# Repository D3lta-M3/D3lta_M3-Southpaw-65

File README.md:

# D3lta_M3 Southpaw 65
 65% keyboard, with either a macropad or a numpad on the left hand side. Uses through-hole for soldering

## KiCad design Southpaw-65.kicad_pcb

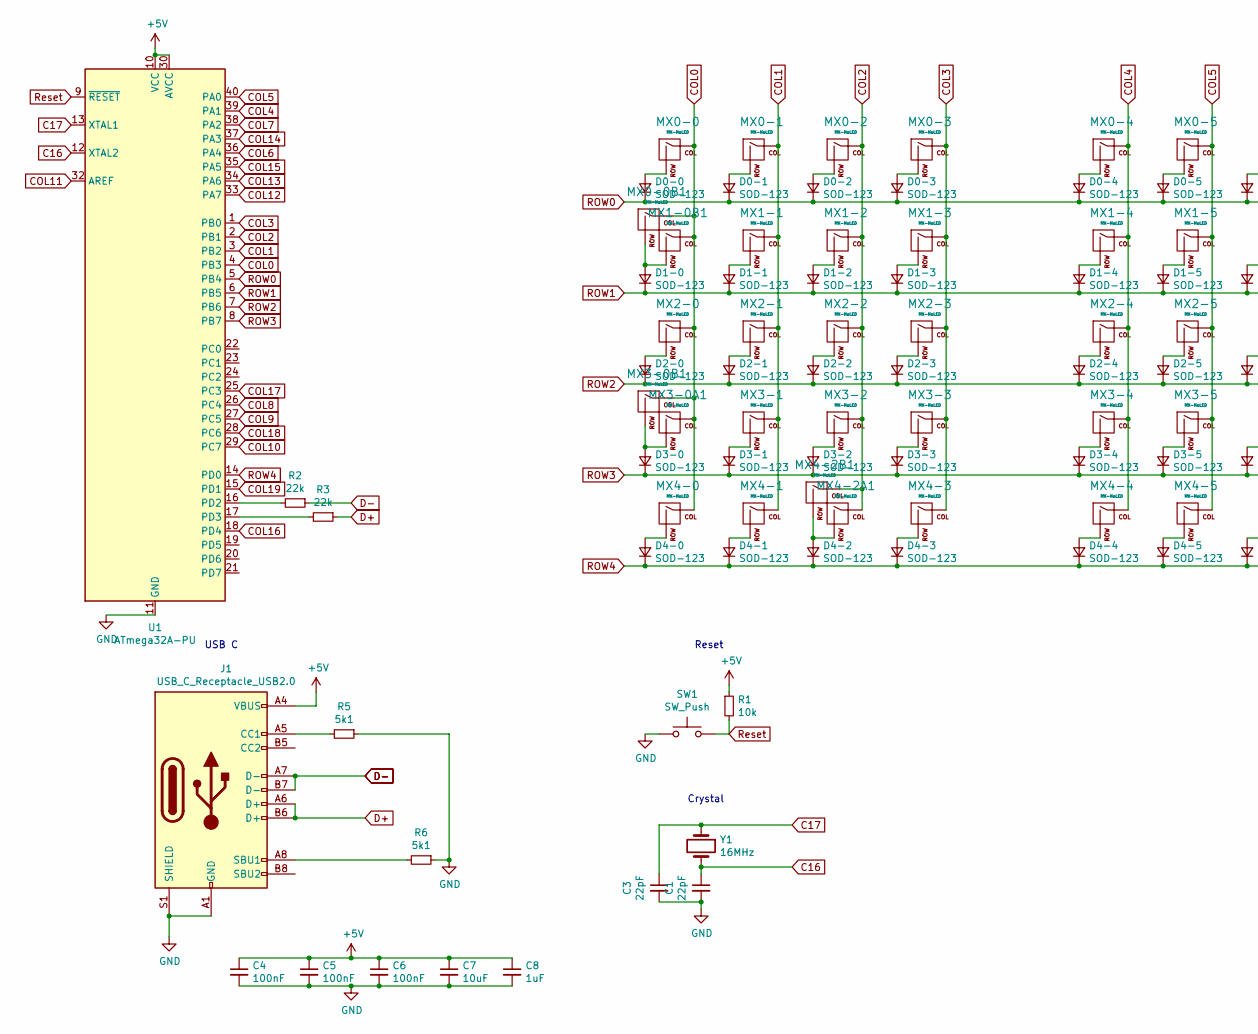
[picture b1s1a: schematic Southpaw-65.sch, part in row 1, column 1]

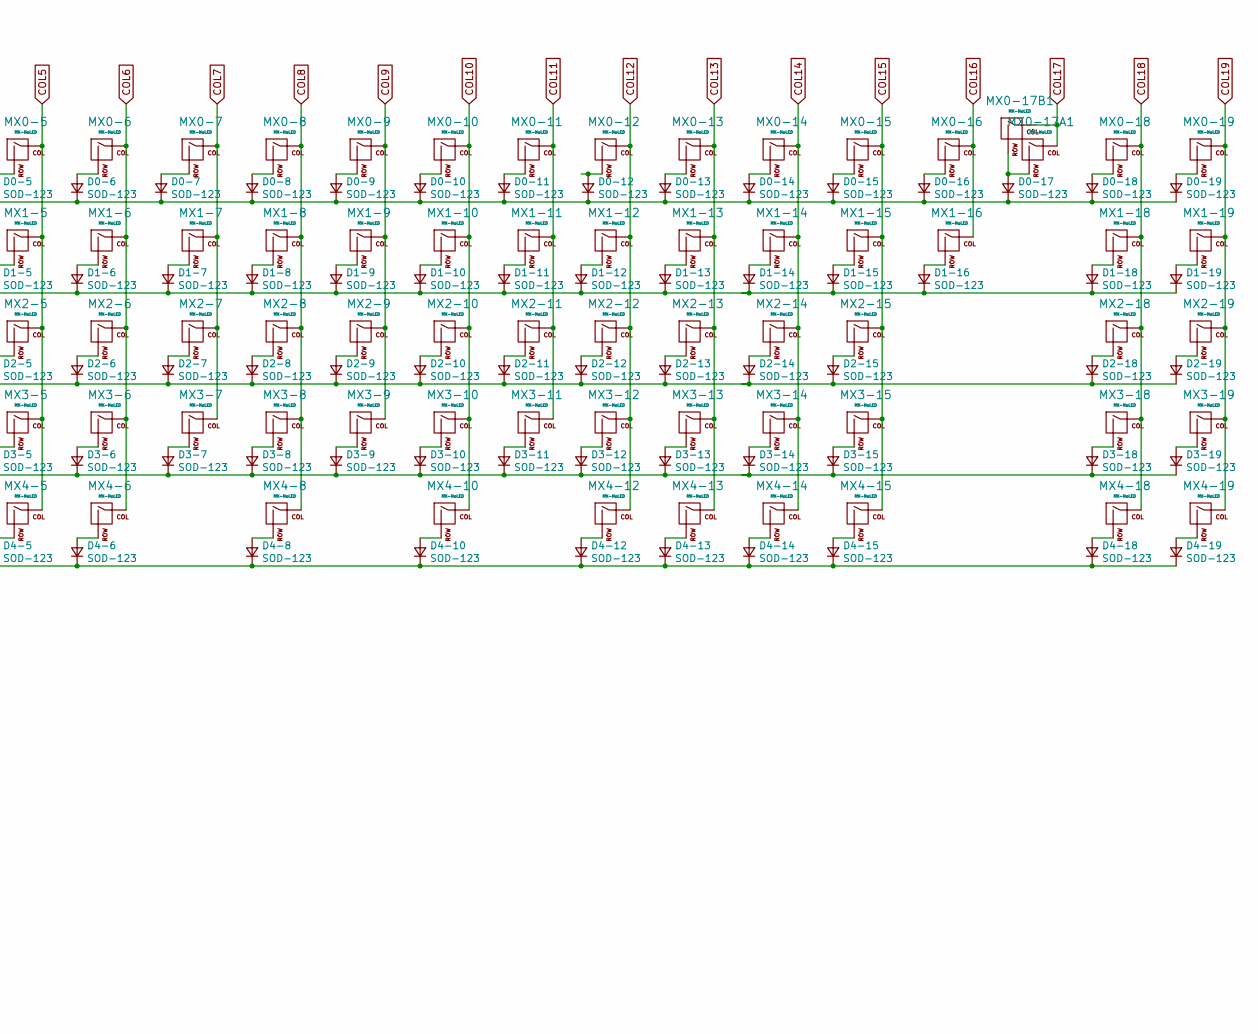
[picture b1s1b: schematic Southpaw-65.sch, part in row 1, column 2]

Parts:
C1, C3: 22pF; CP_Radial_Tantal_D5.0mm_P2.50mm
C4, C5, C6: 100nF; CP_Radial_Tantal_D5.0mm_P2.50mm
C7: 10uF; CP_Radial_Tantal_D5.0mm_P2.50mm
C8: 1uF; CP_Radial_D18.0mm_P7.50mm
D0-0, D0-1, D0-2, D0-3, D0-4, D0-5, D0-6, D0-7, D0-8, D0-9, D0-10, D0-11, D0-12, D0-13, D0-14, D0-15, D0-16, D0-17, D0-18, D0-19, D1-0, D1-1, D1-2, D1-3, D1-4, D1-5, D1-6, D1-7, D1-8, D1-9, D1-10, D1-11, D1-12, D1-13, D1-14, D1-15, D1-16, D1-18, D1-19, D2-0, D2-1, D2-2, D2-3, D2-4, D2-5, D2-6, D2-7, D2-8, D2-9, D2-10, D2-11, D2-12, D2-13, D2-14, D2-15, D2-18, D2-19, D3-0, D3-1, D3-2, D3-3, D3-4, D3-5, D3-6, D3-7, D3-8, D3-9, D3-10, D3-11, D3-12, D3-13, D3-14, D3-15, D3-18, D3-19, D4-0, D4-1, D4-2, D4-3, D4-4, D4-5, D4-6, D4-8, D4-10, D4-12, D4-13, D4-14, D4-15, D4-18, D4-19: SOD-123; D_DO-41_SOD81_P7.62mm_Horizontal
J1: USB_C_Receptacle_USB2.0; USB_C_Receptacle_GCT_USB4085
MX0-0, MX0-1, MX0-2, MX0-3, MX0-4, MX0-5, MX0-6, MX0-7, MX0-8, MX0-9, MX0-10, MX0-11, MX0-12, MX0-13, MX0-14, MX0-15, MX0-16, MX0-17A1, MX0-18, MX0-19, MX1-0B1, MX1-1, MX1-2, MX1-3, MX1-5, MX1-6, MX1-7, MX1-8, MX1-9, MX1-10, MX1-11, MX1-12, MX1-13, MX1-14, MX1-15, MX1-16, MX1-19, MX2-0, MX2-1, MX2-2, MX2-3, MX2-5, MX2-6, MX2-7, MX2-8, MX2-9, MX2-10, MX2-11, MX2-12, MX2-13, MX2-14, MX2-15, MX2-19, MX3-0A1, MX3-1, MX3-2, MX3-3, MX3-5, MX3-6, MX3-7, MX3-8, MX3-9, MX3-10, MX3-11, MX3-12, MX3-13, MX3-14, MX3-18, MX3-19, MX4-0, MX4-1, MX4-2A1, MX4-3, MX4-14, MX4-15, MX4-18, MX4-19: MX-NoLED; MXOnly-1U
MX0-0B1, MX0-17B1, MX3-0B1, MX4-2B1: MX-NoLED; MXOnly-2U
MX1-4, MX1-18: MX-NoLED; MXOnly-1.5U
MX2-4, MX3-15: MX-NoLED; MXOnly-1.75U
MX2-18, MX3-4: MX-NoLED; MXOnly-2.25U
MX4-4, MX4-5, MX4-6, MX4-13: MX-NoLED; MXOnly-1.25U
MX4-8, MX4-12: MX-NoLED; MXOnly-3U
MX4-10: MX-NoLED; MXOnly-7U
R1: 10k; R_Axial_DIN0207_L6.3mm_D2.5mm_P7.62mm_Horizontal
R2, R3: 22k; R_Axial_DIN0207_L6.3mm_D2.5mm_P7.62mm_Horizontal
R5, R6: 5k1; R_Axial_DIN0207_L6.3mm_D2.5mm_P7.62mm_Horizontal
SW1: SW_Push; PushButton_6x6mm_TH
U1: ATmega32A-PU; DIP-40_W15.24mm
Y1: 16MHz; Crystal_HC49-U_Horizontal

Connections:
+5V: C4.1, C5.1, C6.1, C7.1, C8.1, J1.A4 (VBUS), J1.A9 (VBUS), J1.B4 (VBUS), J1.B9 (VBUS), R1.1, U1.10 (VCC), U1.30 (AVCC)
C16: C1.1, U1.12 (XTAL2), Y1.2
C17: C3.1, U1.13 (XTAL1), Y1.1
COL0: MX0-0.1 (COL), MX0-0B1.1 (COL), MX1-0B1.1 (COL), MX2-0.1 (COL), MX3-0A1.1 (COL), MX3-0B1.1 (COL), MX4-0.1 (COL), U1.4 (PB3)
COL1: MX0-1.1 (COL), MX1-1.1 (COL), MX2-1.1 (COL), MX3-1.1 (COL), MX4-1.1 (COL), U1.3 (PB2)
COL2: MX0-2.1 (COL), MX1-2.1 (COL), MX2-2.1 (COL), MX3-2.1 (COL), MX4-2A1.1 (COL), MX4-2B1.1 (COL), U1.2 (PB1)
COL3: MX0-3.1 (COL), MX1-3.1 (COL), MX2-3.1 (COL), MX3-3.1 (COL), MX4-3.1 (COL), U1.1 (PB0)
COL4: MX0-4.1 (COL), MX1-4.1 (COL), MX2-4.1 (COL), MX3-4.1 (COL), MX4-4.1 (COL), U1.39 (PA1)
COL5: MX0-5.1 (COL), MX1-5.1 (COL), MX2-5.1 (COL), MX3-5.1 (COL), MX4-5.1 (COL), U1.40 (PA0)
COL6: MX0-6.1 (COL), MX1-6.1 (COL), MX2-6.1 (COL), MX3-6.1 (COL), MX4-6.1 (COL), U1.36 (PA4)
COL7: MX0-7.1 (COL), MX1-7.1 (COL), MX2-7.1 (COL), MX3-7.1 (COL), U1.38 (PA2)
COL8: MX0-8.1 (COL), MX1-8.1 (COL), MX2-8.1 (COL), MX3-8.1 (COL), MX4-8.1 (COL), U1.26 (PC4)
COL9: MX0-9.1 (COL), MX1-9.1 (COL), MX2-9.1 (COL), MX3-9.1 (COL), U1.27 (PC5)
COL10: MX0-10.1 (COL), MX1-10.1 (COL), MX2-10.1 (COL), MX3-10.1 (COL), MX4-10.1 (COL), U1.29 (PC7)
COL11: MX0-11.1 (COL), MX1-11.1 (COL), MX2-11.1 (COL), MX3-11.1 (COL), U1.32 (AREF)
COL12: MX0-12.1 (COL), MX1-12.1 (COL), MX2-12.1 (COL), MX3-12.1 (COL), MX4-12.1 (COL), U1.33 (PA7)
COL13: MX0-13.1 (COL), MX1-13.1 (COL), MX2-13.1 (COL), MX3-13.1 (COL), MX4-13.1 (COL), U1.34 (PA6)
COL14: MX0-14.1 (COL), MX1-14.1 (COL), MX2-14.1 (COL), MX3-14.1 (COL), MX4-14.1 (COL), U1.37 (PA3)
COL15: MX0-15.1 (COL), MX1-15.1 (COL), MX2-15.1 (COL), MX3-15.1 (COL), MX4-15.1 (COL), U1.35 (PA5)
COL16: MX0-16.1 (COL), MX1-16.1 (COL), U1.18 (PD4)
COL17: MX0-17A1.1 (COL), MX0-17B1.1 (COL), U1.25 (PC3)
COL18: MX0-18.1 (COL), MX1-18.1 (COL), MX2-18.1 (COL), MX3-18.1 (COL), MX4-18.1 (COL), U1.28 (PC6)
COL19: MX0-19.1 (COL), MX1-19.1 (COL), MX2-19.1 (COL), MX3-19.1 (COL), MX4-19.1 (COL), U1.15 (PD1)
D+: J1.A6 (D+), J1.B6 (D+), R3.1
D-: J1.A7 (D-), J1.B7 (D-), R2.1
GND: C1.2, C3.2, C4.2, C5.2, C6.2, C7.2, C8.2, J1.A1 (GND), J1.A12 (GND), J1.B1 (GND), J1.B12 (GND), J1.S1 (SHIELD), R5.1, R6.1, SW1.1, U1.11 (GND), U1.31 (GND)
unnamed: D0-0.2 (A), MX0-0.2 (ROW)
unnamed: D0-1.2 (A), MX0-1.2 (ROW)
unnamed: D0-2.2 (A), MX0-2.2 (ROW)
unnamed: D0-3.2 (A), MX0-3.2 (ROW)
unnamed: D0-4.2 (A), MX0-4.2 (ROW)
unnamed: D0-5.2 (A), MX0-5.2 (ROW)
unnamed: D0-6.2 (A), MX0-6.2 (ROW)
unnamed: D0-7.2 (A), MX0-7.2 (ROW)
unnamed: D0-8.2 (A), MX0-8.2 (ROW)
unnamed: D0-9.2 (A), MX0-9.2 (ROW)
unnamed: D0-10.2 (A), MX0-10.2 (ROW)
unnamed: D0-11.2 (A), MX0-11.2 (ROW)
unnamed: D0-12.2 (A), MX0-12.2 (ROW)
unnamed: D0-13.2 (A), MX0-13.2 (ROW)
unnamed: D0-14.2 (A), MX0-14.2 (ROW)
unnamed: D0-15.2 (A), MX0-15.2 (ROW)
unnamed: D0-16.2 (A), MX0-16.2 (ROW)
unnamed: D0-17.2 (A), MX0-17A1.2 (ROW), MX0-17B1.2 (ROW)
unnamed: D0-18.2 (A), MX0-18.2 (ROW)
unnamed: D0-19.2 (A), MX0-19.2 (ROW)
unnamed: D1-0.2 (A), MX0-0B1.2 (ROW), MX1-0B1.2 (ROW)
unnamed: D1-1.2 (A), MX1-1.2 (ROW)
unnamed: D1-2.2 (A), MX1-2.2 (ROW)
unnamed: D1-3.2 (A), MX1-3.2 (ROW)
unnamed: D1-4.2 (A), MX1-4.2 (ROW)
unnamed: D1-5.2 (A), MX1-5.2 (ROW)
unnamed: D1-6.2 (A), MX1-6.2 (ROW)
unnamed: D1-7.2 (A), MX1-7.2 (ROW)
unnamed: D1-8.2 (A), MX1-8.2 (ROW)
unnamed: D1-9.2 (A), MX1-9.2 (ROW)
unnamed: D1-10.2 (A), MX1-10.2 (ROW)
unnamed: D1-11.2 (A), MX1-11.2 (ROW)
unnamed: D1-12.2 (A), MX1-12.2 (ROW)
unnamed: D1-13.2 (A), MX1-13.2 (ROW)
unnamed: D1-14.2 (A), MX1-14.2 (ROW)
unnamed: D1-15.2 (A), MX1-15.2 (ROW)
unnamed: D1-16.2 (A), MX1-16.2 (ROW)
unnamed: D1-18.2 (A), MX1-18.2 (ROW)
unnamed: D1-19.2 (A), MX1-19.2 (ROW)
unnamed: D2-0.2 (A), MX2-0.2 (ROW)
unnamed: D2-1.2 (A), MX2-1.2 (ROW)
unnamed: D2-2.2 (A), MX2-2.2 (ROW)
unnamed: D2-3.2 (A), MX2-3.2 (ROW)
unnamed: D2-4.2 (A), MX2-4.2 (ROW)
unnamed: D2-5.2 (A), MX2-5.2 (ROW)
unnamed: D2-6.2 (A), MX2-6.2 (ROW)
unnamed: D2-7.2 (A), MX2-7.2 (ROW)
unnamed: D2-8.2 (A), MX2-8.2 (ROW)
unnamed: D2-9.2 (A), MX2-9.2 (ROW)
unnamed: D2-10.2 (A), MX2-10.2 (ROW)
unnamed: D2-11.2 (A), MX2-11.2 (ROW)
unnamed: D2-12.2 (A), MX2-12.2 (ROW)
unnamed: D2-13.2 (A), MX2-13.2 (ROW)
unnamed: D2-14.2 (A), MX2-14.2 (ROW)
unnamed: D2-15.2 (A), MX2-15.2 (ROW)
unnamed: D2-18.2 (A), MX2-18.2 (ROW)
unnamed: D2-19.2 (A), MX2-19.2 (ROW)
unnamed: D3-0.2 (A), MX3-0A1.2 (ROW), MX3-0B1.2 (ROW)
unnamed: D3-1.2 (A), MX3-1.2 (ROW)
unnamed: D3-2.2 (A), MX3-2.2 (ROW)
unnamed: D3-3.2 (A), MX3-3.2 (ROW)
unnamed: D3-4.2 (A), MX3-4.2 (ROW)
unnamed: D3-5.2 (A), MX3-5.2 (ROW)
unnamed: D3-6.2 (A), MX3-6.2 (ROW)
unnamed: D3-7.2 (A), MX3-7.2 (ROW)
unnamed: D3-8.2 (A), MX3-8.2 (ROW)
unnamed: D3-9.2 (A), MX3-9.2 (ROW)
unnamed: D3-10.2 (A), MX3-10.2 (ROW)
unnamed: D3-11.2 (A), MX3-11.2 (ROW)
unnamed: D3-12.2 (A), MX3-12.2 (ROW)
unnamed: D3-13.2 (A), MX3-13.2 (ROW)
unnamed: D3-14.2 (A), MX3-14.2 (ROW)
unnamed: D3-15.2 (A), MX3-15.2 (ROW)
unnamed: D3-18.2 (A), MX3-18.2 (ROW)
unnamed: D3-19.2 (A), MX3-19.2 (ROW)
unnamed: D4-0.2 (A), MX4-0.2 (ROW)
unnamed: D4-1.2 (A), MX4-1.2 (ROW)
unnamed: D4-2.2 (A), MX4-2A1.2 (ROW), MX4-2B1.2 (ROW)
unnamed: D4-3.2 (A), MX4-3.2 (ROW)
unnamed: D4-4.2 (A), MX4-4.2 (ROW)
unnamed: D4-5.2 (A), MX4-5.2 (ROW)
unnamed: D4-6.2 (A), MX4-6.2 (ROW)
unnamed: D4-8.2 (A), MX4-8.2 (ROW)
unnamed: D4-10.2 (A), MX4-10.2 (ROW)
unnamed: D4-12.2 (A), MX4-12.2 (ROW)
unnamed: D4-13.2 (A), MX4-13.2 (ROW)
unnamed: D4-14.2 (A), MX4-14.2 (ROW)
unnamed: D4-15.2 (A), MX4-15.2 (ROW)
unnamed: D4-18.2 (A), MX4-18.2 (ROW)
unnamed: D4-19.2 (A), MX4-19.2 (ROW)
unnamed: J1.A5 (CC1), R5.2
unnamed: J1.A8 (SBU1), R6.2
unnamed: R2.2, U1.16 (PD2)
unnamed: R3.2, U1.17 (PD3)
ROW0: D0-0.1 (K), D0-1.1 (K), D0-2.1 (K), D0-3.1 (K), D0-4.1 (K), D0-5.1 (K), D0-6.1 (K), D0-7.1 (K), D0-8.1 (K), D0-9.1 (K), D0-10.1 (K), D0-11.1 (K), D0-12.1 (K), D0-13.1 (K), D0-14.1 (K), D0-15.1 (K), D0-16.1 (K), D0-17.1 (K), D0-18.1 (K), D0-19.1 (K), U1.5 (PB4)
ROW1: D1-0.1 (K), D1-1.1 (K), D1-2.1 (K), D1-3.1 (K), D1-4.1 (K), D1-5.1 (K), D1-6.1 (K), D1-7.1 (K), D1-8.1 (K), D1-9.1 (K), D1-10.1 (K), D1-11.1 (K), D1-12.1 (K), D1-13.1 (K), D1-14.1 (K), D1-15.1 (K), D1-16.1 (K), D1-18.1 (K), D1-19.1 (K), U1.6 (PB5)
ROW2: D2-0.1 (K), D2-1.1 (K), D2-2.1 (K), D2-3.1 (K), D2-4.1 (K), D2-5.1 (K), D2-6.1 (K), D2-7.1 (K), D2-8.1 (K), D2-9.1 (K), D2-10.1 (K), D2-11.1 (K), D2-12.1 (K), D2-13.1 (K), D2-14.1 (K), D2-15.1 (K), D2-18.1 (K), D2-19.1 (K), U1.7 (PB6)
ROW3: D3-0.1 (K), D3-1.1 (K), D3-2.1 (K), D3-3.1 (K), D3-4.1 (K), D3-5.1 (K), D3-6.1 (K), D3-7.1 (K), D3-8.1 (K), D3-9.1 (K), D3-10.1 (K), D3-11.1 (K), D3-12.1 (K), D3-13.1 (K), D3-14.1 (K), D3-15.1 (K), D3-18.1 (K), D3-19.1 (K), U1.8 (PB7)
ROW4: D4-0.1 (K), D4-1.1 (K), D4-2.1 (K), D4-3.1 (K), D4-4.1 (K), D4-5.1 (K), D4-6.1 (K), D4-8.1 (K), D4-10.1 (K), D4-12.1 (K), D4-13.1 (K), D4-14.1 (K), D4-15.1 (K), D4-18.1 (K), D4-19.1 (K), U1.14 (PD0)
Reset: R1.2, SW1.2, U1.9 (~RESET)

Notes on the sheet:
Crystal
USB C
Reset

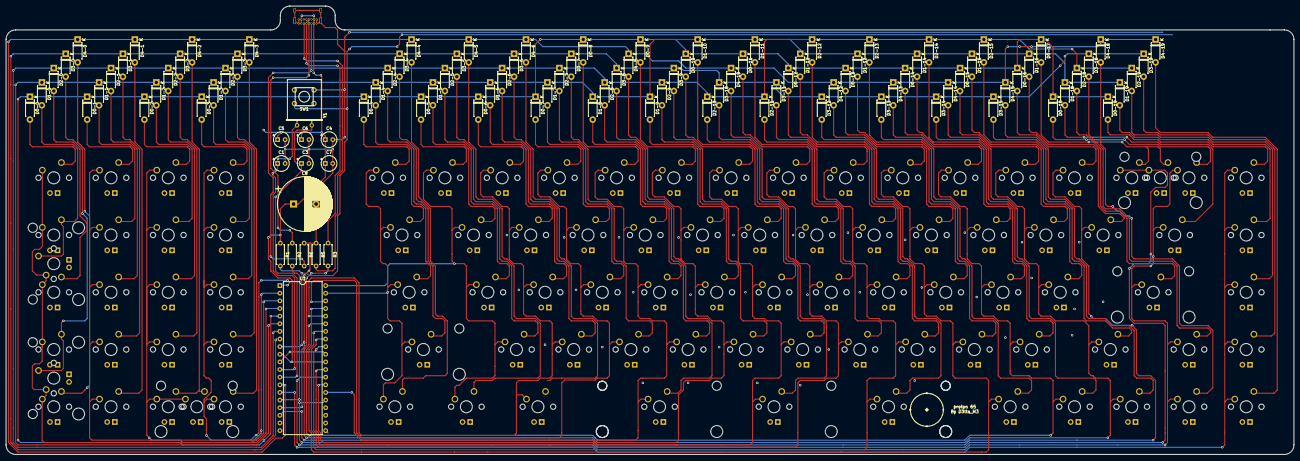
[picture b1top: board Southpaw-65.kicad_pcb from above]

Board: 2 copper layers, 428.6 x 149.2 mm, 200 parts (1 on the bottom side), 126 nets.

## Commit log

2020-10-13 Creation of the Kicad File
2020-10-13 Imported data footprints
2020-10-13 Added libraries
2020-10-13 Completed MCU Zone
2020-10-14 Leftpad and top row added
2020-10-14 Finished switch matrix
2020-10-14 Redid matrix
2020-10-14 Set footprints for everything but crystal
2020-10-16 Connected Matrix to Atmega
2020-10-18 Backup #1
2020-10-19 Set footprints for everything but switches and capcitators
2020-10-20 Set keys
2020-10-20 Re-ogranized the parts and finalized layout
2020-10-21 Labeled the Diodes and reorganized the layout
2020-10-21 Backup #2
2020-10-22 Added capacitators and created top row in pcbnew
2020-10-22 Arranged the switches on the PCB
2020-10-22 Backup #3
2020-10-25 Started tracing and working on pathing
2020-10-26 Finished all tracks
2020-10-27 Added mounting holes to pcb added changed dimensions of PCB
2020-10-29 Backup #4
2020-11-04 Redoing Board
2020-11-05 Made the switch matrix in the pcb
2020-11-05 Added some diodes into matrix
2020-11-05 Added more diodes into the matrix
2020-11-06 Finished Diode Matrix
2020-11-08 More diodes
2020-11-08 Finished all connections from switches to diodes
2020-11-08 Started routing the wiring for the capacitors and diodes
2020-11-09 Wiring switches together
2020-11-09 Did more wiring
2020-11-09 Just a backup
2020-11-10 More wiring
2020-11-11 Lots of wiring to MCU done
    Considering redoing it because thicc bottom
2020-11-11 Redid wirings
    Decrease in space between pcb bottom, and switches
2020-11-13 Added encoders
2020-11-16 Finished encoders and worked on fills
2020-11-18 Finishing Touches
2021-01-26 Redid the outline for the keyboard to make it easier
2021-01-27 Altered bottom row layout and equalized dimensions of board
    Left and right side of board were of different distances from the switches, so they were fixed to be equal. Bottom Row layout is now 1.25/12.5/1.25 rather than 1.5/1/1.25 this does not change the tot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
2021-01-28 Minor Changes
    Consistent edges added as well as removed unnecescary things
2021-01-31 Changed the position of some diodes
2021-02-01 Changed Color and connected keys
2021-02-17 Undid USB as to flip it to other side
2021-02-24 Switched the side which the USB is supposed to lie on
